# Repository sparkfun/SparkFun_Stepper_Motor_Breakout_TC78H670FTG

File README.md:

SparkFun Mini Stepper Motor Driver - TC78H670FTG
========================================

[*SparkFun Mini Stepper Motor Driver - TC78H670FTG (ROB-25167)*](https://sparkle.sparkfun.com/sparkle/products/25167)

The SparkFun Mini Stepper Motor Driver makes it easy to start developing with the TC78H670FTG bipolar stepper motor driver from Toshiba! With its compact size *(0.6" × 0.8")* and 0.1" pin spacing, the Mini Stepper Motor Driver is perfect for small projects or prototyping on breadboards. Use our extensive [Arduino Library](https://github.com/sparkfun/SparkFun_ProDriver_TC78H670FTG_Arduino_Library) with 10 examples, and you can quickly explore the many features of this precise and small package size motor driver IC.

With a high resolution motor control, down to 1/128th of a step, the Mini Stepper Motor Driver can be operated through traditional clock-in stepping or serial commands. Both methods are demonstrated in our Arduino Library. The serial command method is especially unique in that it allows the user to precisely control the phase, torque, current limit and mixed decay ratio of each coil immediately during stepping. Most stepper motor driver ICs require the use of an external trimpot to set the current limit, but with the Mini Stepper Motor Driver, you can precisely adjust it in software, via serial commands!

Repository Contents
-------------------

* **/Documentation** - Datasheets, additional product information
* **/Hardware** - Eagle design files (.brd, .sch)
* **/Hardware/Production** - Production panel files and gerbers (.brd)

Documentation
--------------

* **[Hookup Guide](https://learn.sparkfun.com/tutorials/1200)** - A hookup guide for the SparkFun ProDriver and Mini Stepper Motor Driver (TC78H670FTG)
* **[Arduino Library](https://github.com/sparkfun/SparkFun_ProDriver_TC78H670FTG_Arduino_Library)** - Basic Arduino Library for the SparkFun ProDriver and Mini Stepper Motor Driver (TC78H670FTG)

Product Variants
----------------
* SparkFun Mini Stepper Motor Driver - TC78H670FTG
  * [ROB-25167](https://www.sparkfun.com/products/25167)- v1.0, Initial Release
* SparkFun ProDriver - Stepper Motor Driver (TC78H670FTG)
  * [ROB-16836](https://www.sparkfun.com/products/16836)- v1.0, Initial Release

Product Versions
----------------
* [v01](https://github.com/sparkfun/SparkFun_Stepper_Motor_Breakout_TC78H670FTG/releases/tag/v10) - Initial Release

License Information
-------------------

This product is _**open source**_!

Please review the LICENSE.md file for license information.

If you have any questions or concerns on licensing, please contact technical support on our [SparkFun forums](https://forum.sparkfun.com/viewforum.php?f=152).

Distributed as-is; no warranty is given.

- Your friends at SparkFun.

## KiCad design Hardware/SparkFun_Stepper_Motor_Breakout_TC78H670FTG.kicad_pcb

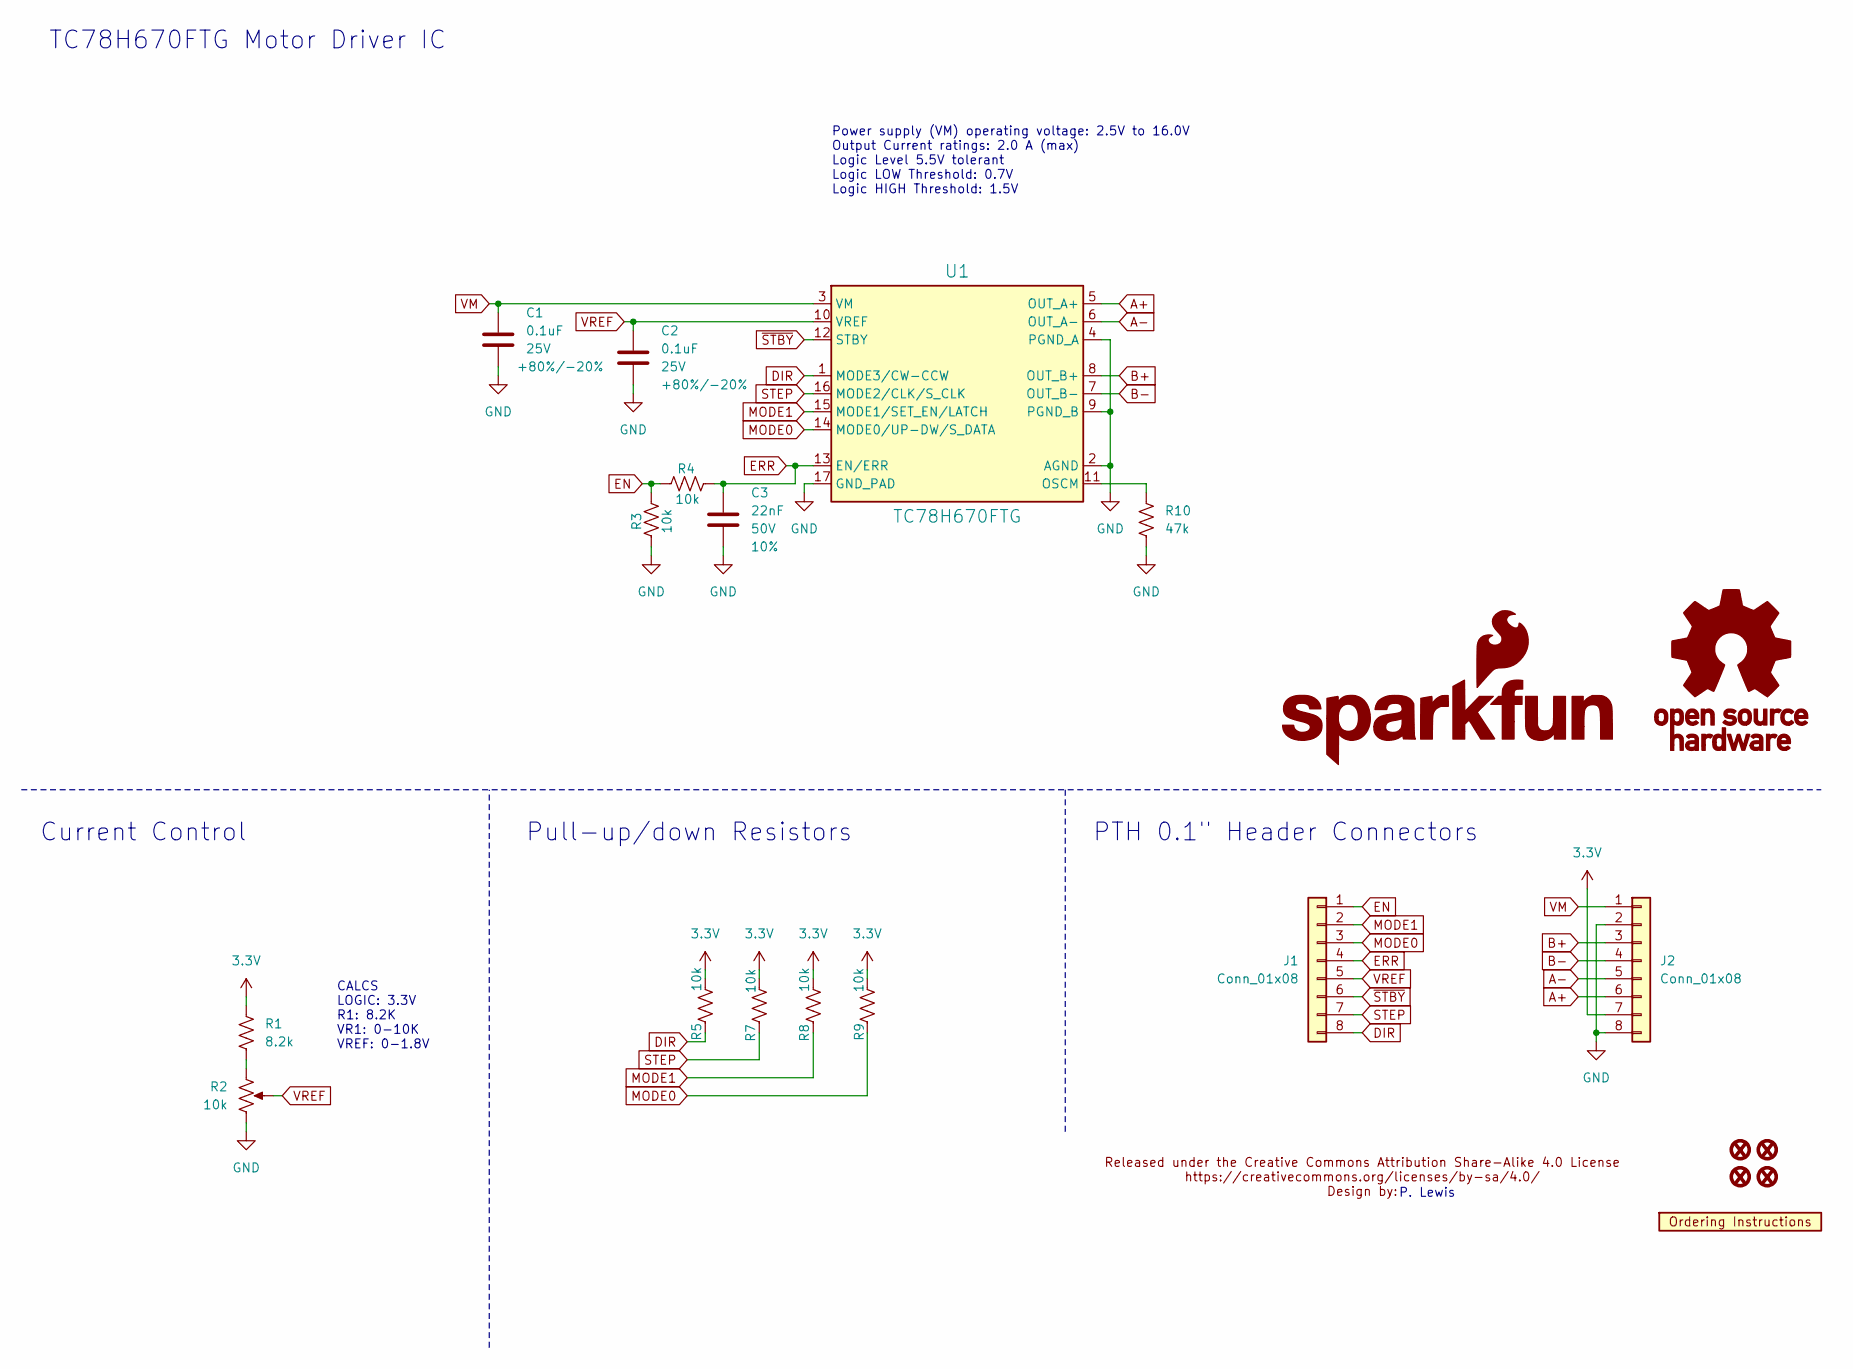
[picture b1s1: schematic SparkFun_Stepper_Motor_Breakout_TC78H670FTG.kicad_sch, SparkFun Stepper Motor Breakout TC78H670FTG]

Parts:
C1, C2: 0.1uF; C_0603_1608Metric; Voltage 25V; Tolerance +80%/-20%
C3: 22nF; C_0603_1608Metric; Voltage 50V; Tolerance 10%
FID1, FID2, FID3, FID4: Fiducial_0.5mm; Fiducial_0.5mm_Mask1mm
G1: SparkFun_Logo
G2: OSHW_Logo; Creative_Commons_License
J1: Conn_01x08; 1x08
J2: Conn_01x08; 1X08
R1: 8.2k; R_0603_1608Metric
R2: 10k; Trimpot_SMD_3.0x3.0mm; Mfg Part# 22AR10K
R3, R4, R5, R7, R8, R9: 10k; R_0603_1608Metric
R10: 47k; R_0603_1608Metric
U1: TC78H670FTG; P-VQFN16-0303-0.50-001
U2: Ordering_Instructions
ref**1: val**; Creative_Commons_License

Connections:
3.3V: J2.7, R1.1, R5.1, R7.1, R8.1, R9.1
A+: J2.6, U1.5 (OUT_A+)
A-: J2.5, U1.6 (OUT_A-)
B+: J2.3, U1.8 (OUT_B+)
B-: J2.4, U1.7 (OUT_B-)
DIR: J1.8, R5.2, U1.1 (MODE3/CW-CCW)
EN: J1.1, R3.1, R4.2
ERR: C3.1, J1.4, R4.1, U1.13 (EN/ERR)
GND: C1.2, C2.2, C3.2, J2.2, J2.8, R2.3, R3.2, R10.2, U1.2 (AGND), U1.4 (PGND_A), U1.9 (PGND_B), U1.17 (GND_PAD)
MODE0: J1.3, R9.2, U1.14 (MODE0/UP-DW/S_DATA)
MODE1: J1.2, R8.2, U1.15 (MODE1/SET_EN/LATCH)
unnamed: R1.2, R2.1
unnamed: R10.1, U1.11 (OSCM)
STEP: J1.7, R7.2, U1.16 (MODE2/CLK/S_CLK)
VM: C1.1, J2.1, U1.3 (VM)
VREF: C2.1, J1.5, R2.2, U1.10 (VREF)
~STBY: J1.6, U1.12 (STBY)

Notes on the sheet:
Current Control
P. Lewis
Pull-up/down Resistors
CALCS LOGIC: 3.3V R1: 8.2K VR1: 0-10K VREF: 0-1.8V
Power supply (VM) operating voltage: 2.5V to 16.0V Output Current ratings: 2.0 A (max) Logic Level 5.5V tolerant Logic LOW Threshold: 0.7V Logic HIGH Threshold: 1.5V
PTH 0.1" Header Connectors
TC78H670FTG Motor Driver IC

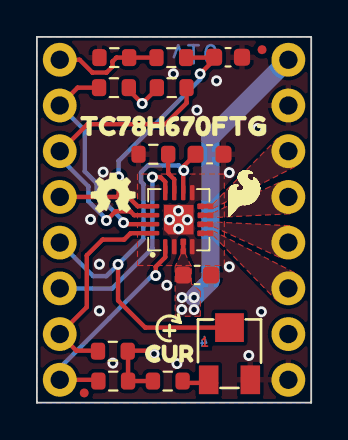
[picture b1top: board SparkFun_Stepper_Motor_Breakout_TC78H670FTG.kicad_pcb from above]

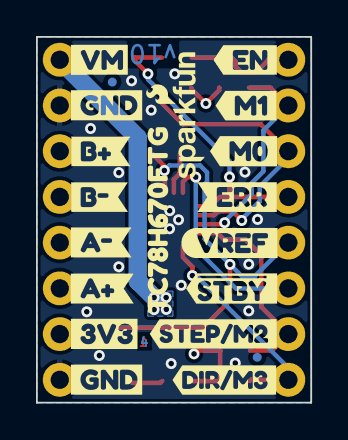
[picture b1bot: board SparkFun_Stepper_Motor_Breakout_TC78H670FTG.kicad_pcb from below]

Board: 4 copper layers, 15.2 x 20.3 mm, 42 parts (19 on the bottom side), 17 nets.

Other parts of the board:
Ref**: Val**; OSHW_Logo_2.5mm
kibuzzard-65CFAA22: G***; kibuzzard-65CFAA22
kibuzzard-65CFAA33, kibuzzard-65CFAA33#2: G***; kibuzzard-65CFAA33
kibuzzard-65CFAAF8: G***; kibuzzard-65CFAAF8
kibuzzard-65CFAB5A: G***; kibuzzard-65CFAB5A
kibuzzard-65CFAB77: G***; kibuzzard-65CFAB77
kibuzzard-65CFAB85: G***; kibuzzard-65CFAB85
kibuzzard-65CFAC2F: G***; kibuzzard-65CFAC2F
kibuzzard-65CFAC5D: G***; kibuzzard-65CFAC5D
kibuzzard-65CFAC9C: G***; kibuzzard-65CFAC9C
kibuzzard-65CFAC13: G***; kibuzzard-65CFAC13
kibuzzard-65CFAC42: G***; kibuzzard-65CFAC42
kibuzzard-65CFAD2C: G***; kibuzzard-65CFAD2C
kibuzzard-65CFAE3D: G***; kibuzzard-65CFAE3D
kibuzzard-65CFAE6E, kibuzzard-65CFAE6E#2: G***; kibuzzard-65CFAE6E
kibuzzard-65D52B03: G***; kibuzzard-65D52B03
kibuzzard-65D52B32: G***; kibuzzard-65D52B32
kibuzzard-65D531EE: G***; kibuzzard-65D531EE

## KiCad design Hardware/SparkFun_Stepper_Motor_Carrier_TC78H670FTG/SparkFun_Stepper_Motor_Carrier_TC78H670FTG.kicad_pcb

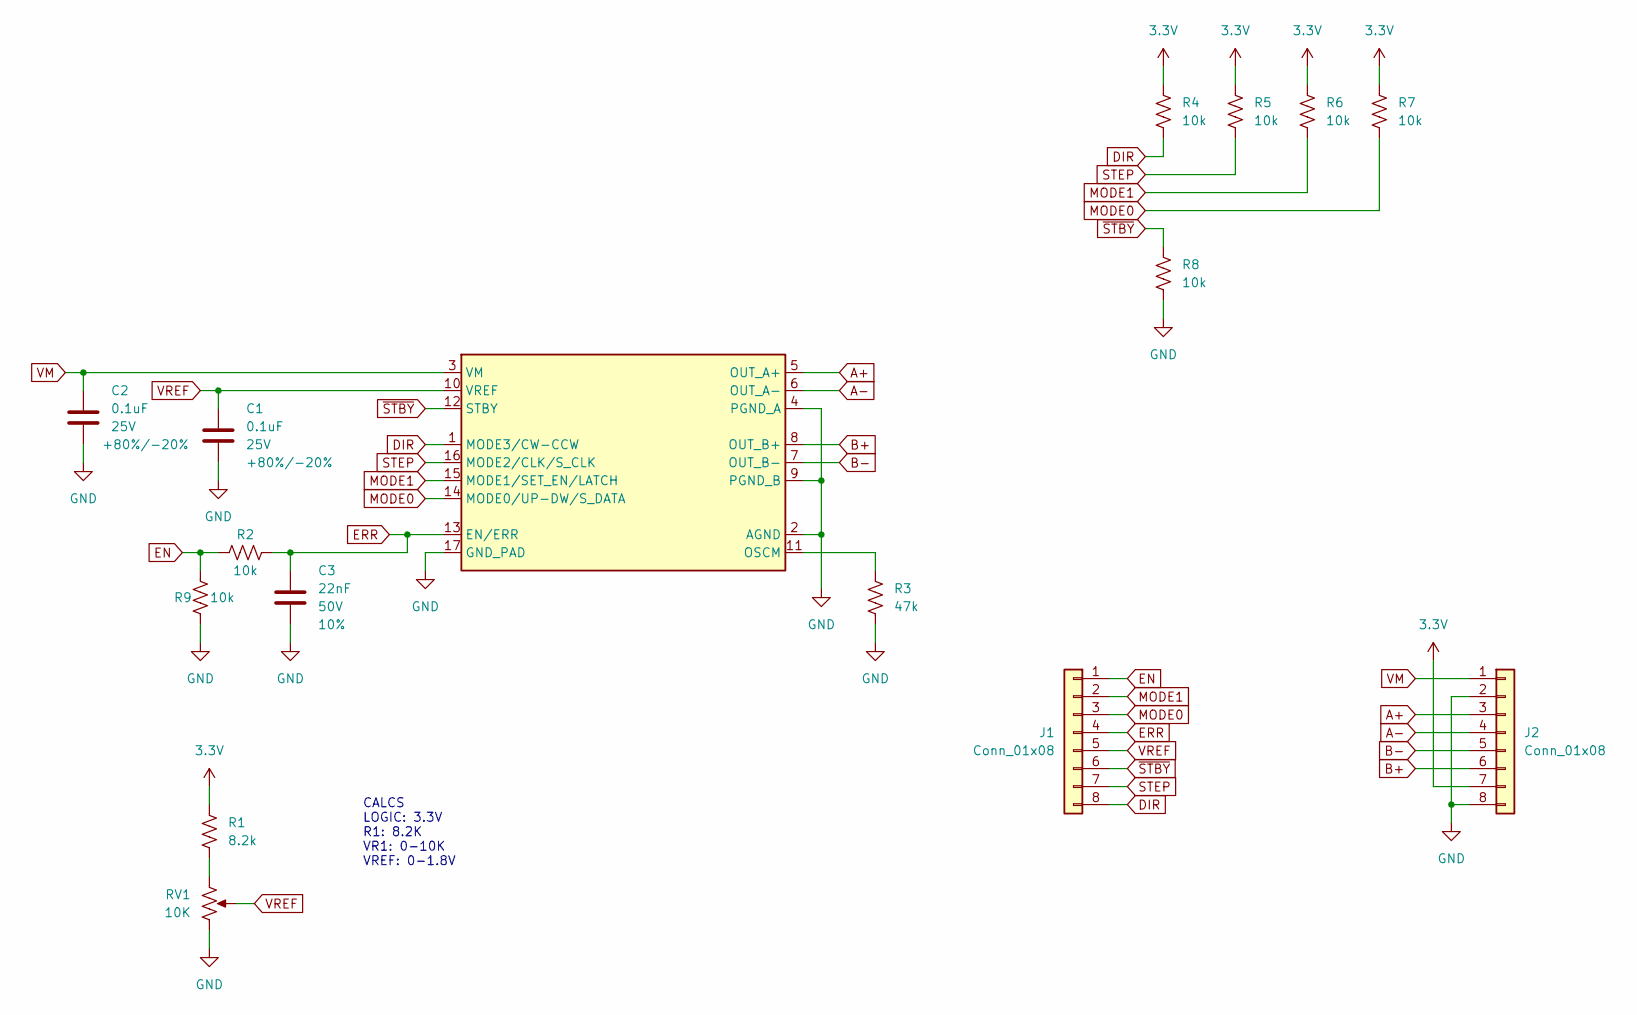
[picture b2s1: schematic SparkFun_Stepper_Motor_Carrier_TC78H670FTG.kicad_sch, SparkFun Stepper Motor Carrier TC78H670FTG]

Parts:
C1, C2: 0.1uF; C_0603_1608Metric; Voltage 25V; Tolerance +80%/-20%
C3: 22nF; C_0603_1608Metric; Voltage 50V; Tolerance 10%
J1, J2: Conn_01x08; 1X08
R1: 8.2k; R_0603_1608Metric
R2, R4, R5, R6, R7, R8, R9: 10k; R_0603_1608Metric
R3: 47k; R_0603_1608Metric
RV1: 10K; TRIMPOT-SMD-3MM-CLOSED
U1: P-VQFN16-0303-0.50-001

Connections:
3.3V: J2.7, R1.1, R4.1, R5.1, R6.1, R7.1
A+: J2.3, U1.5 (OUT_A+)
A-: J2.4, U1.6 (OUT_A-)
B+: J2.6, U1.8 (OUT_B+)
B-: J2.5, U1.7 (OUT_B-)
DIR: J1.8, R4.2, U1.1 (MODE3/CW-CCW)
EN: J1.1, R2.2, R9.1
ERR: C3.1, J1.4, R2.1, U1.13 (EN/ERR)
GND: C1.2, C2.2, C3.2, J2.2, J2.8, R3.2, R8.2, R9.2, RV1.3, U1.2 (AGND), U1.4 (PGND_A), U1.9 (PGND_B), U1.17 (GND_PAD)
MODE0: J1.3, R7.2, U1.14 (MODE0/UP-DW/S_DATA)
MODE1: J1.2, R6.2, U1.15 (MODE1/SET_EN/LATCH)
unnamed: R1.2, RV1.1
unnamed: R3.1, U1.11 (OSCM)
STEP: J1.7, R5.2, U1.16 (MODE2/CLK/S_CLK)
VM: C2.1, J2.1, U1.3 (VM)
VREF: C1.1, J1.5, RV1.2, U1.10 (VREF)
~STBY: J1.6, R8.1, U1.12 (STBY)

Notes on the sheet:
CALCS LOGIC: 3.3V R1: 8.2K VR1: 0-10K VREF: 0-1.8V

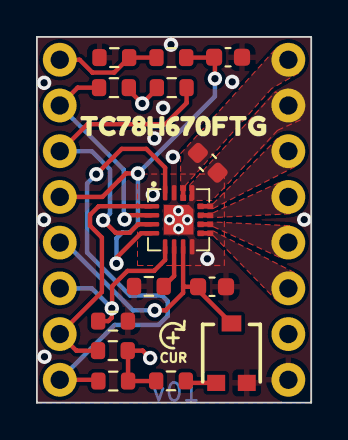
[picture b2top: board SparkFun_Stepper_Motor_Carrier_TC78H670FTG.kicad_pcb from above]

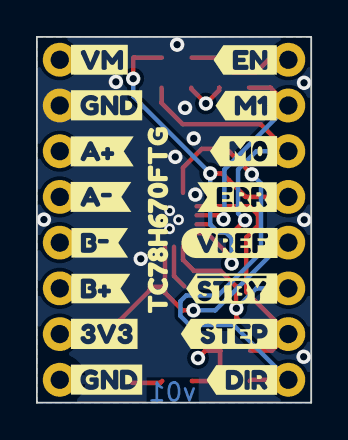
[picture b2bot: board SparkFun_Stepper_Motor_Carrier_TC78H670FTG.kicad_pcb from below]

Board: 4 copper layers, 15.2 x 20.3 mm, 34 parts (17 on the bottom side), 17 nets.

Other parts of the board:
kibuzzard-65CFAA22: G***; kibuzzard-65CFAA22
kibuzzard-65CFAA33, kibuzzard-65CFAA33#2: G***; kibuzzard-65CFAA33
kibuzzard-65CFAAF8: G***; kibuzzard-65CFAAF8
kibuzzard-65CFAB5A: G***; kibuzzard-65CFAB5A
kibuzzard-65CFAB77: G***; kibuzzard-65CFAB77
kibuzzard-65CFAB85: G***; kibuzzard-65CFAB85
kibuzzard-65CFAC2F: G***; kibuzzard-65CFAC2F
kibuzzard-65CFAC5D: G***; kibuzzard-65CFAC5D
kibuzzard-65CFAC9C: G***; kibuzzard-65CFAC9C
kibuzzard-65CFAC13: G***; kibuzzard-65CFAC13
kibuzzard-65CFAC42: G***; kibuzzard-65CFAC42
kibuzzard-65CFAD2C: G***; kibuzzard-65CFAD2C
kibuzzard-65CFAD5D: G***; kibuzzard-65CFAD5D
kibuzzard-65CFAD73: G***; kibuzzard-65CFAD73
kibuzzard-65CFAE3D: G***; kibuzzard-65CFAE3D
kibuzzard-65CFAE6E, kibuzzard-65CFAE6E#2: G***; kibuzzard-65CFAE6E

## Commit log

2024-02-16 initial layout
2024-02-16 version in bottom copper
2024-02-19 spoke angle fix on trimpot footprint
2024-02-19 gitignore
2024-02-19 removed project directory
    -all files are now directly in "hardware" folder
2024-02-19 review notes round 1
    -SCH
    --general cleanup
    --fiducials
    --section lines
    --SFE logo
    --OSHW logo
2024-02-19 dimensions
2024-02-20 sch max voltage note
    -and more gitignore
2024-02-20 schematic cleanup
    -section titles
2024-02-20 more stuff pre-review
    -copper weight added to ordering instructions
    -removed old sym library from project table (eagle import from older prodriver)
    -added CC license to sch
    -added M2 and M3 to buzzard labels for STEP and DIR
    -copper edge clearance in DRC set to 0.2mm
    -excluded DRC errors that I wish to ignore
2024-02-21 add sfe flame logo
2024-02-21 DRV exclusions
2024-02-21 changing file names to "breakout"
2024-02-21 more tweaks for DRC
    -inner layer zone properties min width changed from .3 to .2 to allow flow and more thermal spokes on 3v3 header
    -DRC exclusions for fiducials
2024-02-21 drc exclusions
2024-02-21 ordering instructions
    Inner copper weight
    Material: TG135
    Four layer stack-up
2024-02-21 layout tweaks
    -added gnd via near serial data line transition
    -reduced via sized to 12mil to avoid drc errors and make room
2024-02-21 moved fiducials inward
2024-02-22 trimpot datasheet
2024-02-22 updated trimpot
2024-02-22 corrected motor driver IC footprint
    I had the pins numbered incorrectly, had to re-route most things.
2024-02-22 checklist stuff
    -added 1,2,3,4 to copper layers
2024-02-23 nudged VM - bottom gnd flow
2024-02-23 reduced paste on driver IC
2024-02-23 step routed directly away from ic
2024-02-23 more gnd vias
2024-02-23 version to v10
2024-02-23 production panel and gerbers v10c
2024-02-28 library work and sch cleanup
    -moved to a 0.05" grid for schematic and tightened things up (made all nets shorter to match smaller grid and only use a single grid space to extend out from any pin)
    -updated ordering instructions fp to avoid sch->brd update error
2024-03-08 removing duplicate trimpot in PCB file
2024-04-17 Create LICENSE.md
    Remove carriage returns
    Fix grammar
2024-04-17 Add templates
2024-04-17 Update README.md
    Add product information
2024-04-17 Update .gitignore
    Extend backup files

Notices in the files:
Hardware/SparkFun_Stepper_Motor_Breakout_TC78H670FTG.kicad_sch:
Released under the Creative Commons Attribution Share-Alike 4.0 License
https://creativecommons.org/licenses/by-sa/4.0
